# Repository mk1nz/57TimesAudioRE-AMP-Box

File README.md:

# 57TimesAudioRE-AMP-Box
High performance re-amp box using high precission resistors, high quality connectors and Lundahl LL1540 transformer

<br>

Frequency response is around +- 0.2db

<br>
THD 0.071% (about -86.5dbFs at a signal level of -6.6dbFs)<br>
50HZ ripple is at a level of -101.6dbFs.

<br>

# Parts list I used in my build:
  R1, R2 - UXB02070F1202BCU00 Vishay Metal Film Resistors UXB 0207-10 0.1% CU 12K<br>
  R3 - MRS25000C5109FCT00 Vishay Metal Film Resistor - Through Hole MRS25-50 1% CT 51R<br>
  VR1 - P160KNPD-0QC15A10K BI Technologies / TT Electronics Potentiometer, 1/10W 10K Ohms 20% 16mm ROTARY POT<br>
  C1 - FKP3F021003F00KI00 Wima Film Capacitor FKP 3 0.01 uF 250 VDC 5x11x13 PCM 10<br>
  J2 - NRJ6HM-1-PRE Neutrik Phone Connector Jack 1/4" - stereo switched tip and ring (not sleeve), slim-full thread metal-PCBH-cha grd<br>
  J3 - NC3FD-H-B Neutrik XLR Connectors 3C FEMALE PCB BLK/GD<br>
  S1 - DPDT Standard Through Hole PCB Right Angle Push Button Self-lock Switch, similar to 22F02 (Please note that the part number on the schematic is incorrect and differs from that on the Gerber files.)<br>

WARNING: Soldering the pins of the LL1540 should be done as quickly as possible to avoid damaging the transformer. I soldered the transformer at 300 degrees Celsius using high quality flux, applying molten solder to each pin for about 2-3 seconds.

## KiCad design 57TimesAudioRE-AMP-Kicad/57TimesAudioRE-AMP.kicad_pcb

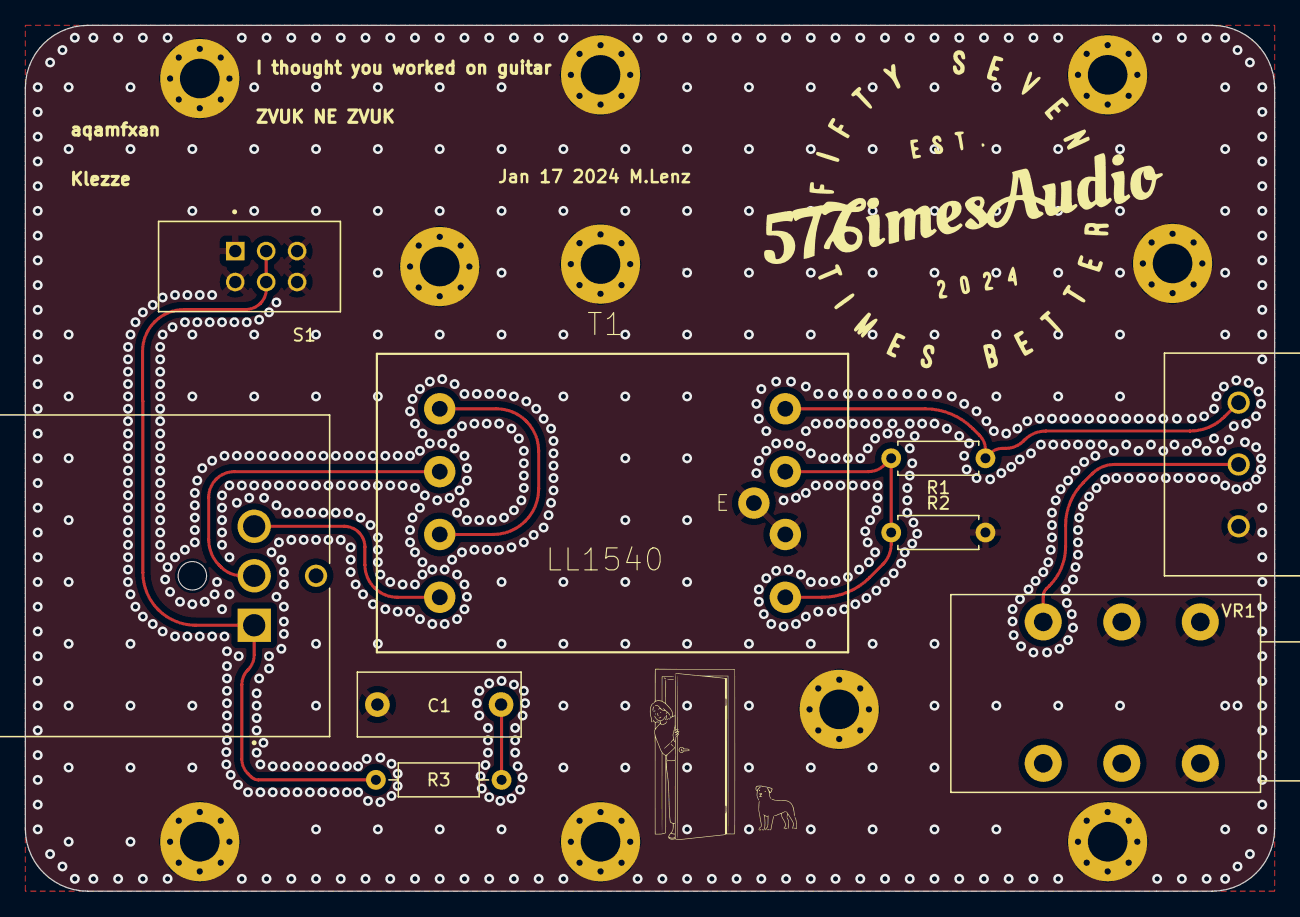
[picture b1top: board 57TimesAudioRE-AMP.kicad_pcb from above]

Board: 2 copper layers, 101.0 x 70.0 mm, 9 parts (0 on the bottom side), 9 nets.

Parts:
C1: 10nf; C_Rect_L13.0mm_W5.0mm_P10.00mm_FKS3_FKP3_MKS4
J2: Jack OUT; Jack_6.35mm_Neutrik_NRJ6HM-1-PRE_Horizontal
J3: NC3FAAH-0; NEUTRIK_NC3FD-H-B
R1, R2: 12k; R_Axial_DIN0207_L6.3mm_D2.5mm_P7.62mm_Horizontal
R3: 51; R_Axial_DIN0207_L6.3mm_D2.5mm_P10.16mm_Horizontal
S1: PushButton Right Angle DPDT; SW_PBH2UEESNPNAGX
T1: LL1540; LUNDAHL-LL1540
VR1: P160KN-0QC15A10K; P160

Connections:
GND: C1.2, J2.R, J2.S, R2.2, S1.1, S1.3, S1.4, S1.6, T1.6, T1.E, VR1.1
unnamed: C1.1, R3.2
unnamed: J2.T, VR1.2
unnamed: J3.1, R3.1, S1.2, S1.5
unnamed: J3.2, T1.1
unnamed: J3.3, T1.3
unnamed: R1.1, T1.8, VR1.3
unnamed: R1.2, R2.1, T1.5, T1.7
unnamed: T1.2, T1.4

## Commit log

2025-03-30 Schematic and symbols of the reamp box
2025-03-30 PCB Fabrication files (Gerber)
